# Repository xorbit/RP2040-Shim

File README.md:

# RP2040-Shim
Dual-core ARM Cortex M0+ shim for PoE-FeatherWing, functionally equivalent to Feather RP2040.

With parts for the [M4-Shim](https://www.tindie.com/products/silicognition/m4-shim/) scarce,
it seemed wise to come up with a well-supported alternative.

### Description

This is an adaptation of the excellent
[Adafruit Feather RP2040](https://github.com/adafruit/Adafruit-Feather-RP2040-PCB),
redesigned specifically for use with the equally excellent
[PoE-FeatherWing](https://hackaday.io/project/168356-poe-featherwing).

The goal was to create a compact system with Power over Ethernet, Ethernet connectivity and
a powerful processor capable of supporting [CircuitPython](https://circuitpython.org/).
Because of the bulky RJ45 jack and flyback transformer on the PoE-FeatherWing, it was not
possible to mount a traditional Feather on top.  This redesign takes the relevant circuitry
of the Adafruit Feather RP2040 and shapes it so it fits in the gaps between the
tall components of the PoE-FeatherWing.  This way it can be mounted on top for an extremely
compact solution.

The relevant differences versus the Feather RP2040 are omission of the battery support circuitry
(which did not seem necessary in a PoE design), no Qwiic / STEMMA QT connector, no SWD footprint
and 4 MB of SPI flash.
Note also that the board pins are connected differently to the chip so as to fit the tiny board
area available.  When using CircuitPython, the pins use a custom mapping so the names in the
`board` module map to the same board pins as the Feather RP2040, but when using a different
development environment that uses the RP2040 GPIO pin numbers, you will have to adjust them for
this board.

The hardware is sold with [CircuitPython](https://github.com/adafruit/circuitpython) pre-installed.

### License

This redesign by Silicognition LLC is licensed as Creative Commons Attribution/Share-Alike,
just like the Adafruit Feather RP2040 it is based on.

Original Adafruit license statement:

Feather RP2040

Open source PCB files for Feather RP2040

PCB format is EagleCAD schematic and board layout

For more details, check out the product pages at

    https://www.adafruit.com/products/4884

We are releasing these files so folks can start creating custom designs based on the RP2040 chip. This design has been built and tested successfully

Adafruit invests time and resources providing this open source design, please support Adafruit and open-source hardware by purchasing products from Adafruit!

Designed by Adafruit Industries.
Creative Commons Attribution, Share-Alike license, check license.txt for more information All text above must be included in any redistribution

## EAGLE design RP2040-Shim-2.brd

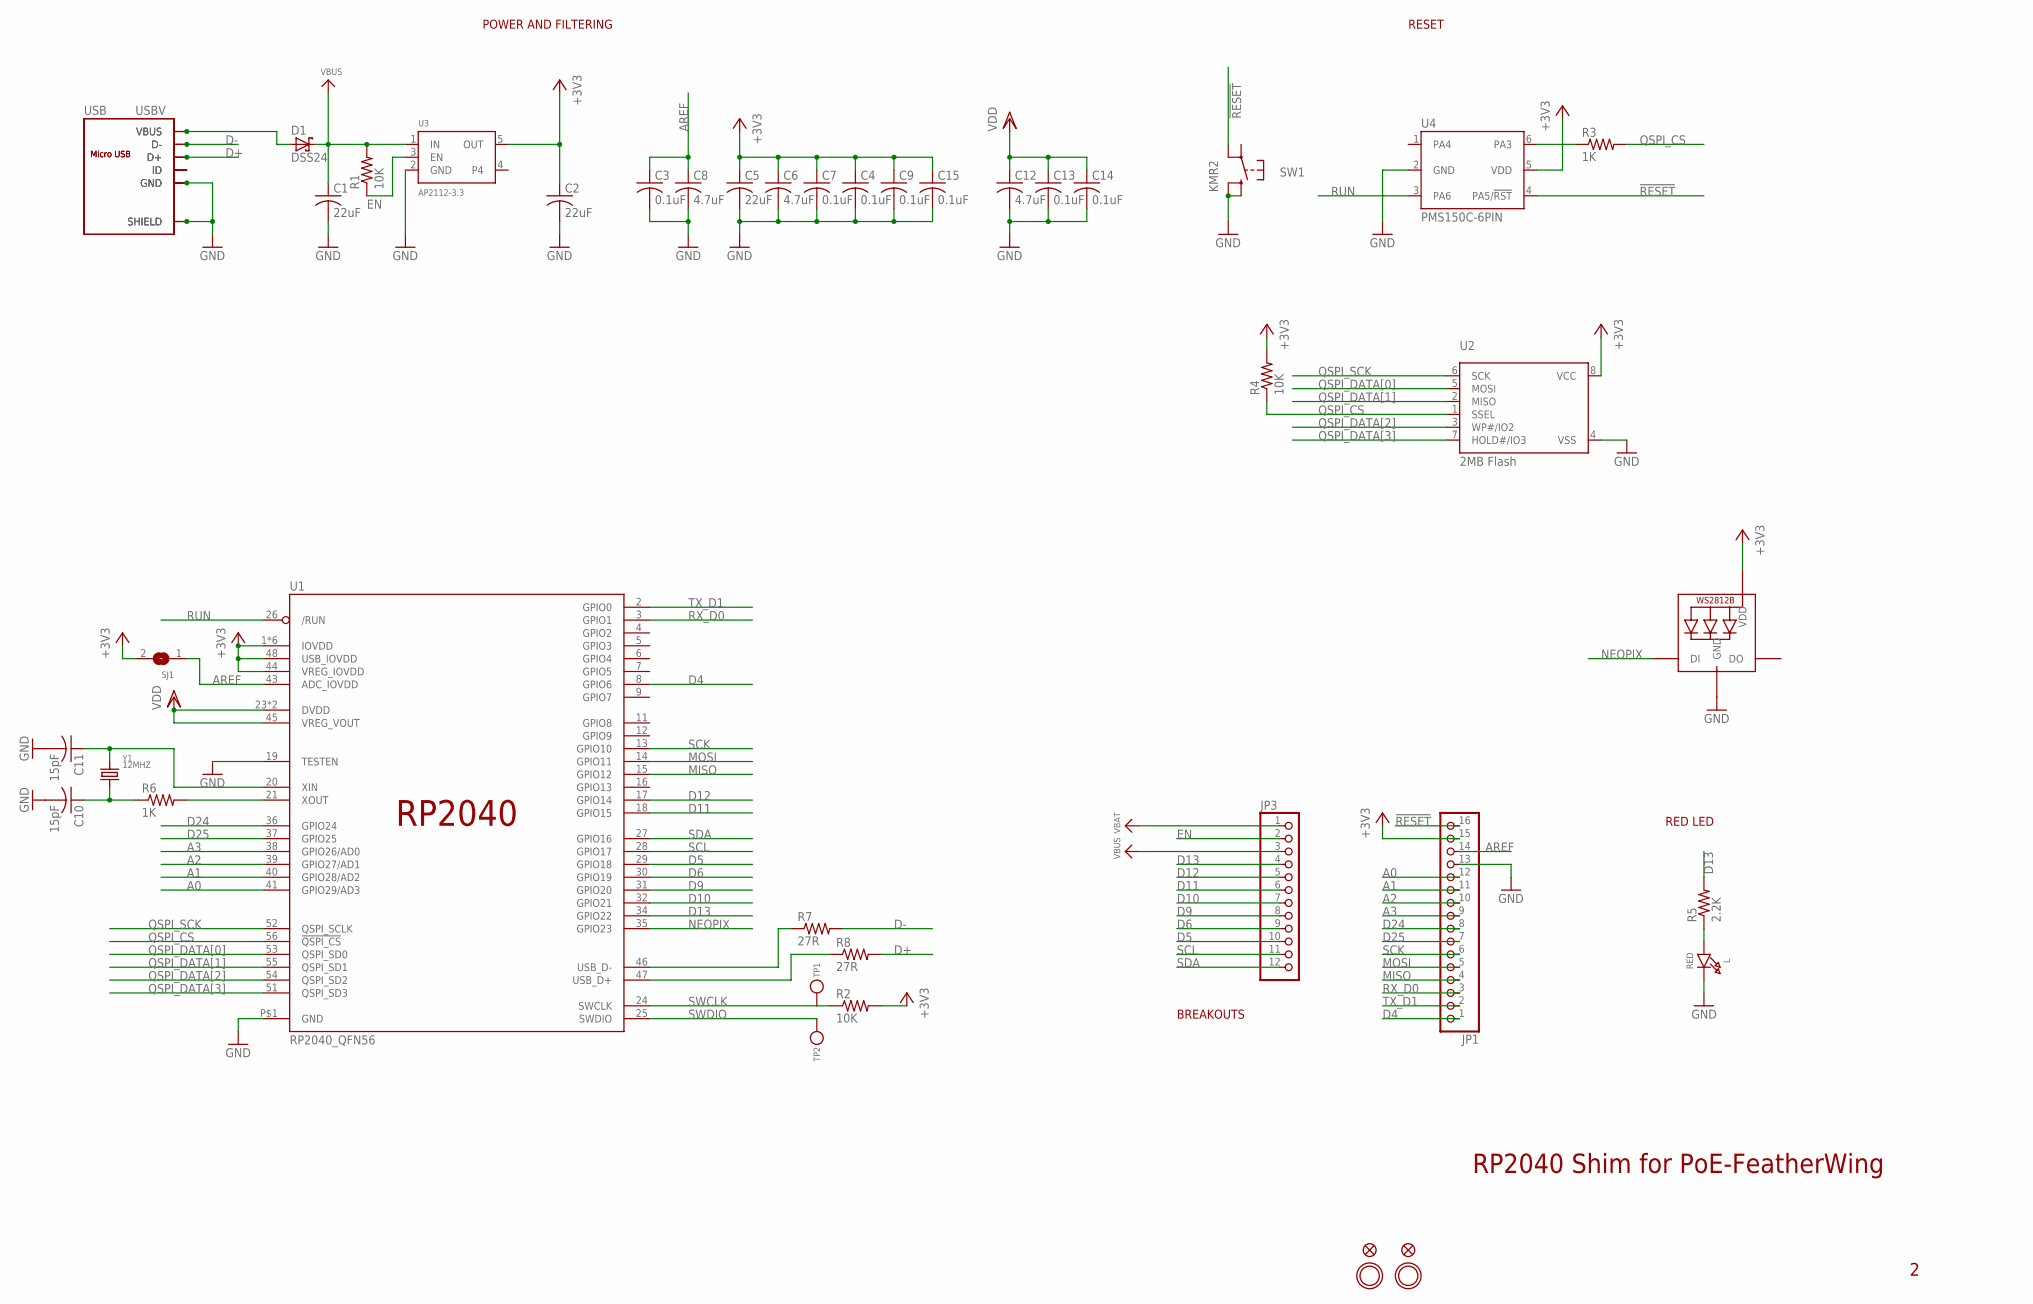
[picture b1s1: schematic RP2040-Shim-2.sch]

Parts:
C1, C2, C5: 22uF; C0805K
C3, C4, C7, C9, C13, C14, C15: 0.1uF; C0402K
C6, C8, C12: 4.7uF; C0402K
C10, C11: 15pF; C0402K
D1: DSS24; SOD123FL
JP1: HEADER-1X16ROUND; 1X16_ROUND
JP3: HEADER-1X12; 1X12_ROUND
L: RED; CHIPLED_0805_NOOUTLINE
LED1: WS2812B3535; LED3535
R1, R2, R4: 10K; R0402
R3, R6: 1K; R0402
R5: 2.2K; R0402
R7, R8: 27R; R0402
SJ1: SOLDERJUMPERCLOSED; SOLDERJUMPER_CLOSEDWIRE
SW1: KMR2; BTN_KMR2_4.6X2.8
TP1, TP2: TESTPOINTROUND1.5MM; TESTPOINT_ROUND_1.5MM
U1: RP2040_QFN56; QFN56_7MM_REDUCEDEPAD
U2: 2MB Flash; USON8
U3: AP2112-3.3; SOT23-5
U4: PMS150C-6PIN; SOT23-6
U$31, U$32: MOUNTINGHOLE2.5; MOUNTINGHOLE_2.5_PLATED
U$34, U$35: FIDUCIAL_1MM
USB: ZX62-B-5PA; TS-1012E-AC03516
USBV: MICRO-USB-SMD-VERT; U-D-M5DS-W-4
Y1: 12MHZ; CRYSTAL_2.5X2

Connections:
!RESET: JP1.16, SW1.A' (P1), U4.4 (PA5/!RST)
+3V3: C2.1, C4.1, C5.1, C6.1, C7.1, C9.1, C15.1, JP1.15, LED1.2 (VDD), R2.2, R4.2, SJ1.2, U1.1 (IOVDD), U1.10 (IOVDD), U1.22 (IOVDD), U1.33 (IOVDD), U1.42 (IOVDD), U1.44 (VREG_IOVDD), U1.48 (USB_IOVDD), U1.49 (IOVDD), U2.8 (VCC), U3.5 (OUT), U4.5 (VDD)
A0: JP1.12, U1.41 (GPIO29/AD3)
A1: JP1.11, U1.40 (GPIO28/AD2)
A2: JP1.10, U1.39 (GPIO27/AD1)
A3: JP1.9, U1.38 (GPIO26/AD0)
AREF: C3.1, C8.1, JP1.14, SJ1.1, U1.43 (ADC_IOVDD)
D4: JP1.1, U1.8 (GPIO6)
D5: JP3.10, U1.29 (GPIO18)
D6: JP3.9, U1.30 (GPIO19)
D9: JP3.8, U1.31 (GPIO20)
D10: JP3.7, U1.32 (GPIO21)
D11: JP3.6, U1.18 (GPIO15)
D12: JP3.5, U1.17 (GPIO14)
D13: JP3.4, R5.2, U1.34 (GPIO22)
D24: JP1.8, U1.36 (GPIO24)
D25: JP1.7, U1.37 (GPIO25)
D+: R8.2, USB.3 (D+), USBV.3 (D+)
D-: R7.2, USB.2 (D-), USBV.2 (D-)
EN: JP3.2, R1.1, U3.3 (EN)
GND: C1.2, C2.2, C3.2, C4.2, C5.2, C6.2, C7.2, C8.2, C9.2, C10.2, C11.2, C12.2, C13.2, C14.2, C15.2, JP1.13, L.C, LED1.4 (GND), SW1.B (S), SW1.B' (S1), U1.19 (TESTEN), U1.P$1 (GND), U2.4 (VSS), U3.2 (GND), U4.2 (GND), USB.5 (GND), USB.P1 (SHIELD), USB.P2 (SHIELD), USB.P3 (SHIELD), USB.P4 (SHIELD), USB.P5 (SHIELD), USB.P6 (SHIELD), USBV.5 (GND), USBV.MNT1 (SHIELD), USBV.MNT2 (SHIELD), USBV.MNT3 (SHIELD), USBV.MNT4 (SHIELD)
MISO: JP1.4, U1.15 (GPIO12)
MOSI: JP1.5, U1.14 (GPIO11)
unnamed: USB.4 (ID), USBV.4 (ID)
unnamed: L.A, R5.1
unnamed: C10.1, R6.1, Y1.1
unnamed: R6.2, U1.21 (XOUT)
unnamed: C11.1, U1.20 (XIN), Y1.3 (2)
unnamed: R8.1, U1.47 (USB_D+)
unnamed: R7.1, U1.46 (USB_D-)
unnamed: R3.1, U4.6 (PA3)
NEOPIX: LED1.1 (DI), U1.35 (GPIO23)
QSPI_CS: R3.2, R4.1, U1.56 (!QSPI_CS), U2.1 (SSEL)
QSPI_DATA[0]: U1.53 (QSPI_SD0), U2.5 (MOSI)
QSPI_DATA[1]: U1.55 (QSPI_SD1), U2.2 (MISO)
QSPI_DATA[2]: U1.54 (QSPI_SD2), U2.3 (WP#/IO2)
QSPI_DATA[3]: U1.51 (QSPI_SD3), U2.7 (HOLD#/IO3)
QSPI_SCK: U1.52 (QSPI_SCLK), U2.6 (SCK)
RUN: U1.26 (/RUN), U4.3 (PA6)
RX_D0: JP1.3, U1.3 (GPIO1)
SCK: JP1.6, U1.13 (GPIO10)
SCL: JP3.11, U1.28 (GPIO17)
SDA: JP3.12, U1.27 (GPIO16)
SWCLK: R2.1, TP1.P$1, U1.24 (SWCLK)
SWDIO: TP2.P$1, U1.25 (SWDIO)
TX_D1: JP1.2, U1.2 (GPIO0)
VBAT: JP3.1
VBUS: C1.1, D1.C, JP3.3, R1.2, U3.1 (IN)
VBUSEXT: D1.A, USB.1 (VBUS), USBV.1 (VBUS)
VDD: C12.1, C13.1, C14.1, U1.23 (DVDD), U1.45 (VREG_VOUT), U1.50 (DVDD)

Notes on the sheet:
POWER AND FILTERING
RESET
BREAKOUTS
RED LED
RP2040 Shim for PoE-FeatherWing

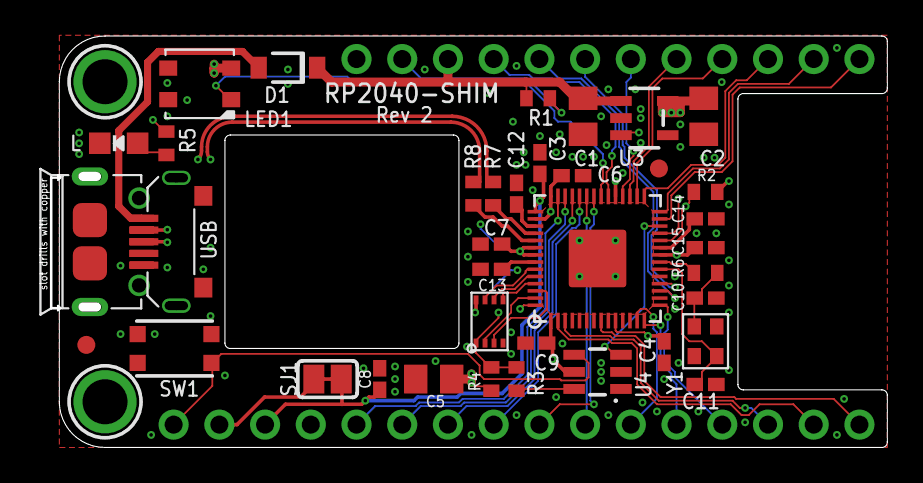
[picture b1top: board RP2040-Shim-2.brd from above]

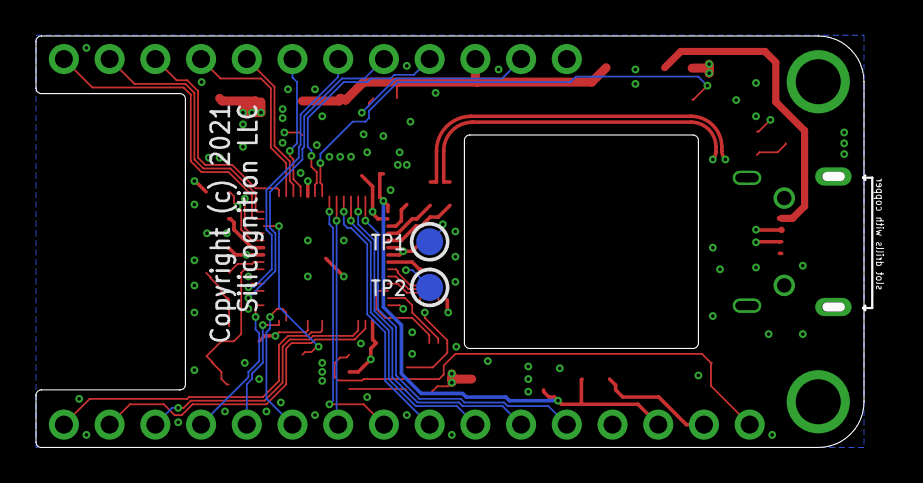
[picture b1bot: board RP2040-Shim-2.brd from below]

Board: 4 copper layers, 46.8 x 22.4 mm, 43 parts (2 on the bottom side), 49 nets.

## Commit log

2022-06-14 Update README to my fork instead of upstream CircuitPython
    This shows the changes to be made to add the board.
2023-01-19 Update README.md
    Point to official Adafruit CircuitPython repo.
2023-07-28 Update README.md to document different pinout
2023-07-28 Update osc caps to 15 pF, add pinout diagram
2023-07-28 Update README.md fix markup

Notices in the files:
RP2040-Shim-2.brd:
Copyright (c) 2021
parts and their libraries:
microbuilder: This work is placed in the public domain, and may be freely used for commercial and non-commercial work with the following conditions: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
